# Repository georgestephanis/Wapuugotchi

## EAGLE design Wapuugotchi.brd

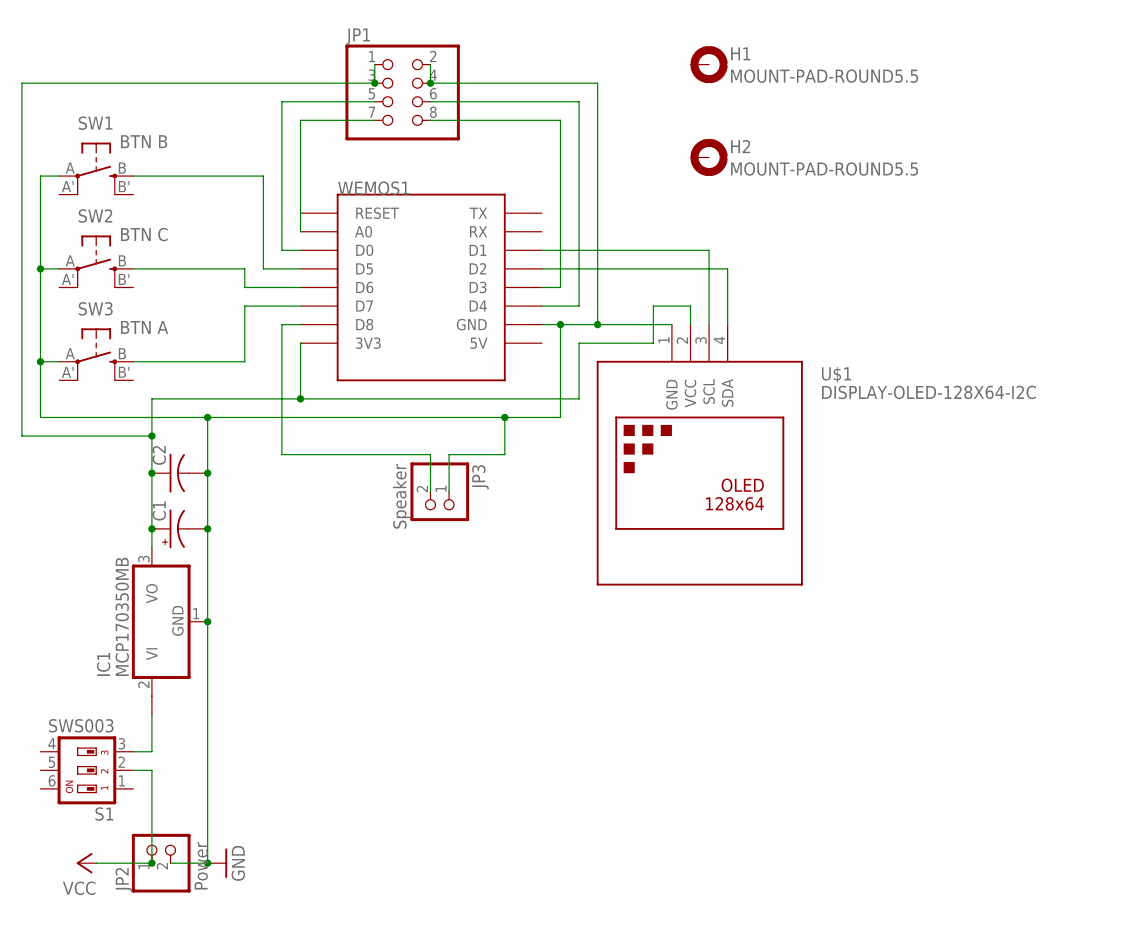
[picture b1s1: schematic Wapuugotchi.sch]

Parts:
C1: CPOL-US153CLV-1012; 153CLV-1012
C2: C-USC0805; C0805
H1, H2: MOUNT-PAD-ROUND5.5; 5,5-PAD
IC1: MCP170350MB; SOT89
JP1: PINHD-2X4; 2X04
JP2: Power; 1X02
JP3: Speaker; 1X02
S1: SWS003; SMS-003
SW1: BTN B; EVQ-Q2
SW2: BTN C; EVQ-Q2
SW3: BTN A; EVQ-Q2
U$1: DISPLAY-OLED-128X64-I2C
WEMOS1: WEMOS-D1-MINI

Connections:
GND: C1.-, C2.2, IC1.1 (GND), JP1.2, JP1.4, JP2.2, JP3.1, SW1.A, SW2.A, SW3.A, U$1.1 (GND), WEMOS1.GND
unnamed: U$1.3 (SCL), WEMOS1.D1
unnamed: U$1.4 (SDA), WEMOS1.D2
unnamed: SW3.B (S), WEMOS1.D7
unnamed: SW2.B (S), WEMOS1.D6
unnamed: SW1.B (S), WEMOS1.D5
unnamed: JP3.2, WEMOS1.D8
unnamed: JP1.7, WEMOS1.A0
unnamed: JP1.5, WEMOS1.D0
unnamed: JP1.8, WEMOS1.D3
unnamed: JP1.6, WEMOS1.D4
unnamed: C1.+, C2.1, IC1.3 (VO), JP1.1, JP1.3, U$1.2 (VCC), WEMOS1.3V3
unnamed: IC1.2@1 (VI1), S1.3
VCC: JP2.1, S1.2

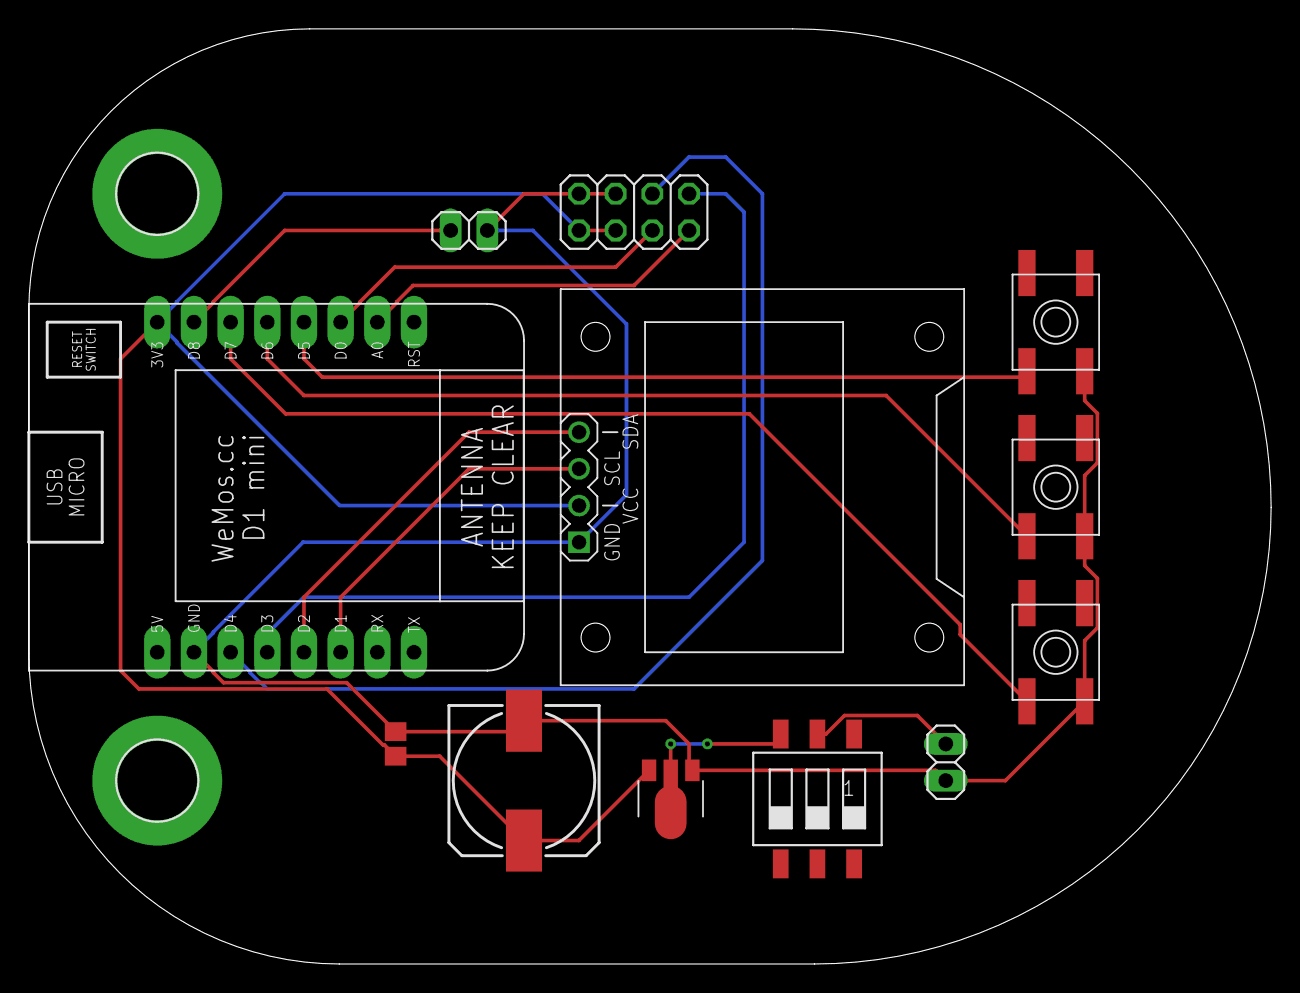
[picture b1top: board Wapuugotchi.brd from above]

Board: 2 copper layers, 86.0 x 64.8 mm, 14 parts (0 on the bottom side), 14 nets.

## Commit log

2018-01-11 Clear out some extraneous comments.
2018-01-11 Check, cache, and display the mac address.
    This will allow each badge to uniquely identify itself for leaderboards.
2018-01-11 Handle button inputs and test usage.
    All seems correct.
2018-01-11 Define a speaker pin for the buzzer.
2018-01-11 Add a wiring and components diagram.
2018-01-12 Add Eagle files for pcb and renderings.
2018-01-13 Update to use debounce library for button presses.
2018-01-16 First draft of Wapuu class.
2018-01-17 Move Wapuu class to seperate file.
2018-01-17 Add SimpleTimer.
2018-01-17 Make sure to do a newline.
2018-01-17 Whitespace.
2018-01-17 Rename and add header.
2018-01-17 Add age tracking.
2018-01-17 Add feed and clean_poop functions.
2018-01-18 Move the reports out for explicitness.
2018-01-18 Clarify mac address.
2018-01-18 Remove needless delay on startup.
2018-01-18 Add getter methods for private variables.
2018-01-18 Remove bmp image for now. Will reimplement later for varied pixel size.
2018-01-18 Add methods for writing data to screen.
2018-02-28 Flip the pins on the buttons.
    I had them going in the wrong order on the board.
2018-02-28 Tweak the hardware to account for how the switch is wired (left side isolated from right)

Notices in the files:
parts and their libraries:
diy-modules: Released under the Creative Commons Attribution 4.0 International License: http://creativecommons.org/licenses/by/4.0
